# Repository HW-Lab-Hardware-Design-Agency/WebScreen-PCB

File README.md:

# WebScreen-PCB

WebScreen-PCB is the design of a printed circuit board (PCB) for the WebScreen, a display device with a custom stand. This project is developed by **HW Lab - Hardware Design Agency** and aims to optimize the integration and functionality of the WebScreen in various applications.

## Main Features
- **Optimized Design**: Compact and efficient PCB. 
- **Mounting System**: Insertion and friction-based fastening, eliminating the need for adhesives. 
- **Compatibility**: Designed to work with the [DO0200FS01 display](https://www.dwo.net.cn/pd.jsp?id=11919).
- **Connectivity**: Interfaces adapted for easy integration with other devices.
  
## Technical Specifications
- **Size**: 60.6 x 27.6 mm
- **Material**: FR-4 S1000H TG150
- **PCB Thickness**: 1.6 mm
- **Number of Layers**: 4 layers
- **Operating Voltage**: 5V (via usb)
- **Connection Interfaces**: USB / Wi-Fi / Bluetooth

## Included Files
- **Schematic**: : Circuit design in [KiCad](https://www.kicad.org/) format. 
- **PCB Layout**: Board design in Gerber format.
- **Bill of Materials (BOM)**: List of components used. 

## Installation and Usage  
1. Download the Gerber files and send them to a PCB manufacturer.  
2. Acquire the components according to the BOM.  
3. Assemble the PCB.  
4. [Integrate the PCB with the WebScreen](https://www.youtube.com/watch?v=CHH5L84EN5o&t=6s) and perform the corresponding tests.

## License
This project is open source. See the [LICENSE](https://github.com/HW-Lab-Hardware-Design-Agency/WebScreen-PCB/blob/main/LICENSE) file for details.

## PCBWay
[PCBWay](https://pcbway.com/g/j8T652) top quality PCBA service made this project possible: fast, precise, and super reliable. We highly recommend them to all creators out there, and we’ll definitely keep working with them for future builds.

## Contact
For inquiries or contributions, please contact the development team through the repository issues or via email.

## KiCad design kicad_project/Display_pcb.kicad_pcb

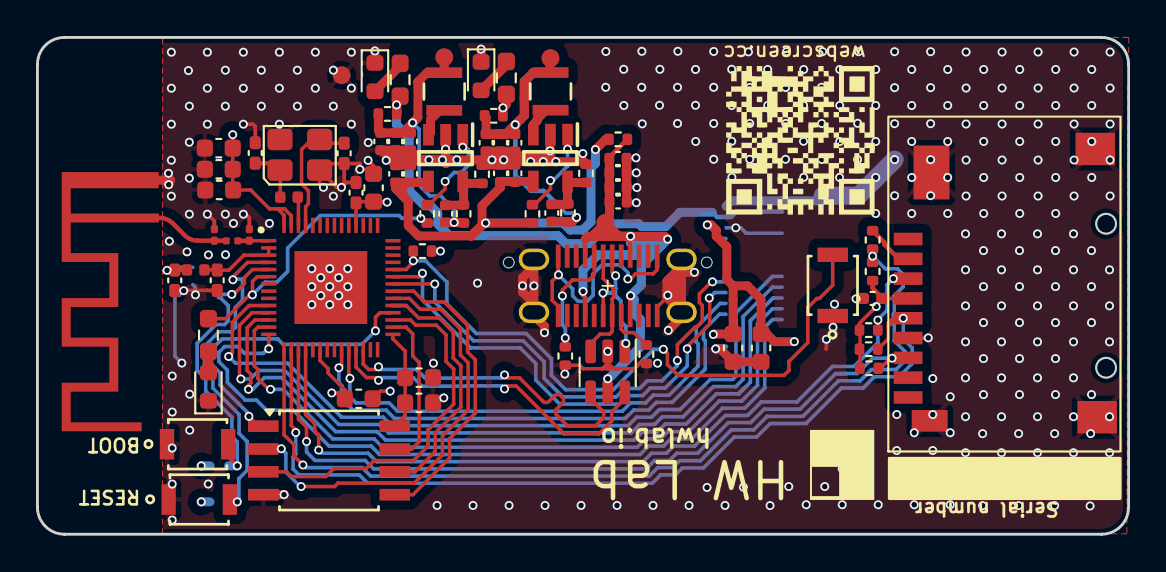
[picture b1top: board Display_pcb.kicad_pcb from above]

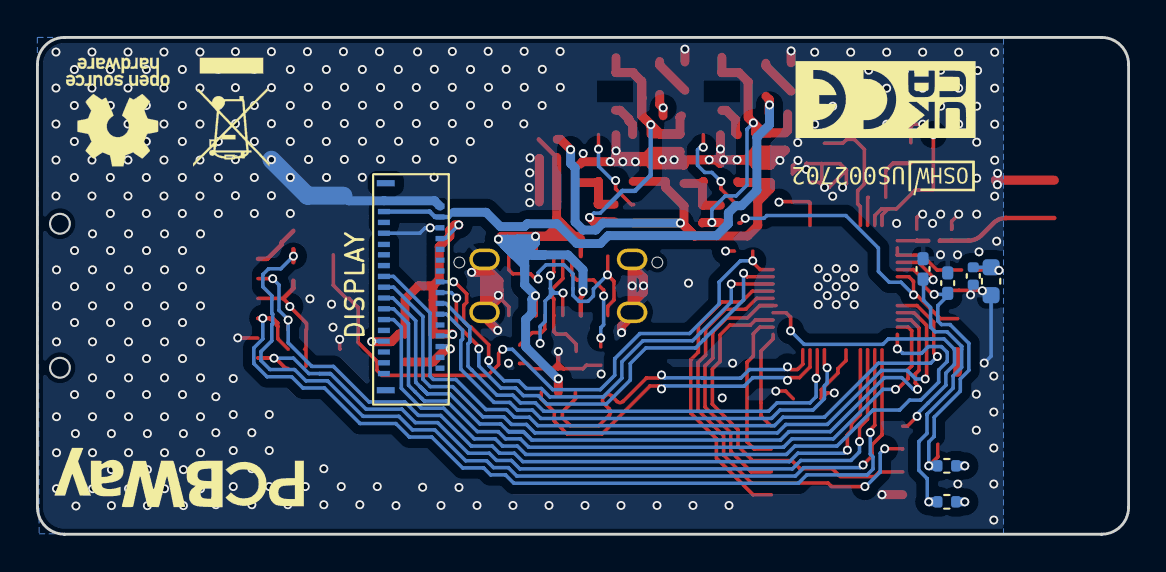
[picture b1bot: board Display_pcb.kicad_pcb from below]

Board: 4 copper layers, 60.6 x 27.6 mm, 86 parts (7 on the bottom side), 56 nets.

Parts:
AE1: PCB Antenna 2.4GHz; pcb_antenna_2_4GHz
C1, C8, C9, C12, C13, C19: 100nF; C_0402_1005Metric_Pad0.74x0.62mm_HandSolder
C2, C5, C6, C7, C10, C14, C15, C20, C32, C33: 1uF; C_0603_1608Metric
C3: 15pF; C_0402_1005Metric_Pad0.74x0.62mm_HandSolder
C4: 12pF; C_0402_1005Metric_Pad0.74x0.62mm_HandSolder
C11: 10uF; C_0402_1005Metric
C16, C17: 1.8pF; C_0201_0603Metric
C18, C22, C24, C25, C27, C28, C30, C34, C36, C37: 22uF; C_0402_1005Metric
C21, C31: 6.8pF; C_0402_1005Metric
C23, C26, C29, C35: 100nF; C_0402_1005Metric
DS1, DS2, DS3: GREEN; LED_0603_1608Metric
IC1: ESP32-S3R8; QFN40P700X700X90-57N-D
J1: Micro_SD_Card_Det_Hirose_DM3AT; TF PUSH
J2: USB C; USB_C_Receptacle_HCTL_HC019-1E1H1A103-0HR
J8: 33FXRH-SM1-GAN-TF
L1: 22nH; L_0402_1005Metric
L2: 2nH; L_0402_1005Metric
L3: 2.7nH; L_0201_0603Metric
L4, L5: 1uH; BR2518_YDN
NT1, NT2: NetTie_2; NetTie-2_SMD_Pad0.5mm
R1, R2, R3, R4, R7, R10, R12, R20: 10k; R_0402_1005Metric
R5, R6: 4k99; R_0402_1005Metric
R8, R18, R19, R32: 0R; R_0402_1005Metric
R9: 64k9; R_0402_1005Metric
R11, R13, R14: 100k; R_0402_1005Metric
R15, R16, R23: 1k; R_0603_1608Metric_Pad0.98x0.95mm_HandSolder
R17: 22k; R_0402_1005Metric
SW1, SW2, SW3: B3U-1000P
TP1: +5V; TestPoint_Pad_D1.0mm
TP2: +4V6; TestPoint_Pad_D1.0mm
TP4: +3V3; TestPoint_Pad_D1.0mm
TP5: GND; TestPoint_Pad_D1.0mm
U1: W25Q128JVSIQ; SOIC-8W_5.3x5.3mm_P1.27mm
U2, U4: SY8089A1AAC; SOT95P285X130-5N
U5: USBLC6-2SC6; SOT-23-6
Y1: 40MHz; SMD32324-4P

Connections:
4.6V: J8.3, J8.4, R16.2, R32.2
+3V3: C1.1, C2.1, C5.1, C6.1, C7.1, C9.1, C10.1, C11.1, C13.1, C15.1, IC1.20 (VDD3P3_RTC), IC1.46 (VDD3P3_CPU), IC1.55 (VDDA_1), IC1.56 (VDDA_2), J1.4 (VDD), J8.8, L2.1, NT1.2, NT2.2, R1.1, R2.1, R3.1, R4.1, R7.1, R12.1, R18.2, R20.1, R23.2
/AVDD: C32.1, J8.27, NT1.1
/CLK: IC1.16 (GPIO11), J1.5 (CLK), R4.2
/CMD: IC1.18 (GPIO13), J1.3 (CMD), R12.2
/CS: IC1.15 (GPIO10), R8.2, R20.2
/D+: J2.A6 (D+), J2.B6 (D+), U5.3 (I/O2)
/D-: J2.A7 (D-), J2.B7 (D-), U5.1 (I/O1)
/DAT0: IC1.17 (GPIO12), J1.7 (DAT0), R3.2
/Flash_Memory/SPICLK: IC1.33 (SPICLK), U1.6 (CLK)
/Flash_Memory/SPICS0: IC1.32 (SPICS0), U1.1 (~CS)
/Flash_Memory/SPID: IC1.35 (SPID), U1.5 (DI(IO0))
/Flash_Memory/SPIHD: IC1.30 (SPIHD), U1.7 (IO3)
/Flash_Memory/SPIQ: IC1.34 (SPIQ), U1.2 (DO(IO1))
/Flash_Memory/SPIWP: IC1.31 (SPIWP), U1.3 (IO2)
/MCU/GPIO0: C19.1, IC1.5 (GPIO0), R2.2, SW2.2
/MCU/GPIO1: IC1.6 (GPIO1), R11.2, R15.2
/MCU/GPIO33: IC1.38 (GPIO33), R7.2, SW3.2
/MCU/LNA: C16.1, IC1.1 (LNA_IN), L3.2
/MCU/LNA_IN: AE1.1 (FP), C17.1, L3.1
/OL_CS: IC1.11 (GPIO6), J8.17
/OL_D0: IC1.24 (GPIO18), J8.20
/OL_D1: IC1.12 (GPIO7), J8.19
/OL_D2: IC1.36 (SPICLK_N), J8.16
/OL_D3: IC1.10 (GPIO5), J8.15
/OL_RESET: IC1.23 (GPIO17), J8.22
/OL_SCK: IC1.37 (SPICLK_P), J8.18
/OL_SD0: IC1.13 (GPIO8), J8.21
/OL_TE: IC1.14 (GPIO9), J8.23
/POWER/VBUS: C18.1, C27.1, C28.1, C37.1, J2.A4 (VBUS), J2.A9 (VBUS), J2.B4 (VBUS), J2.B9 (VBUS), R19.1, TP1.1, U5.5 (VBUS)
/USB+: IC1.26 (GPIO20), U5.4 (I/O2)
/USB-: IC1.25 (GPIO19), U5.6 (I/O1)
GND: AE1.2 (GND), C1.2, C2.2, C3.2, C4.2, C5.2, C6.2, C7.2, C8.2, C9.2, C10.2, C11.2, C12.2, C13.2, C14.2, C15.2, C16.2, C17.2, C18.2, C19.2, C20.2, C22.2, C23.2, C24.2, C25.2, C26.2, C27.2, C28.2, C29.2, C30.2, C32.2, C33.2, C34.2, C35.2, C36.2, C37.2, DS1.1 (K), DS2.1 (K), DS3.1 (K), IC1.57 (EP), J1.6 (VSS), J1.11 (SHIELD), J2.A1 (GND), J2.S1 (SHIELD), J8.1, J8.2, J8.6, J8.7, J8.28, R5.2, R6.2, R10.2, R17.2, SW1.1, SW2.1, SW3.1, TP5.1, U1.4 (GND), U2.2 (GND), U4.2 (GND), U5.2 (GND), Y1.2, Y1.4
unnamed: C4.1, L1.1, Y1.1
unnamed: C21.1, C22.1, C23.1, C24.1, L5.2, R9.1, R32.1, TP2.1
unnamed: C31.1, C34.1, C35.1, C36.1, L4.2, R14.1, R18.1, TP4.1
unnamed: DS1.2 (A), R15.1
unnamed: DS2.2 (A), R16.1
unnamed: DS3.2 (A), R23.1
unnamed: C12.1, IC1.4 (CHIP_PU), R1.2, SW1.2
unnamed: C8.1, IC1.2 (VDD3P3_1), IC1.3 (VDD3P3_2), L2.2
unnamed: C3.1, IC1.53 (XTAL_N), Y1.3
unnamed: IC1.54 (XTAL_P), L1.2
unnamed: J1.2 (DAT3/CD), R8.1
unnamed: J2.A5 (CC1), R6.1
unnamed: J2.B5 (CC2), R5.1
unnamed: J2.A12 (GND), J2.B1 (GND), J2.B12 (GND)
unnamed: C33.1, J8.26, NT2.1
unnamed: R11.1, U2.1 (EN)
unnamed: C21.2, R9.2, R10.1, U2.5 (FB)
unnamed: L5.1, U2.3 (LX)
unnamed: R13.1, U4.1 (EN)
unnamed: C31.2, R14.2, R17.1, U4.5 (FB)
unnamed: L4.1, U4.3 (LX)
VCC: C25.1, C26.1, C29.1, C30.1, R13.2, R19.2, U2.4 (IN), U4.4 (IN)
VDD_SPI: C14.1, C20.1, IC1.29 (VDD_SPI), U1.8 (VCC)

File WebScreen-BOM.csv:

Reference,Value,Qty,DNP,BOM,LCSC Part #,MPN
AE1,PCB Antenna 2.4GHz,1,,,,
"C1,C8,C9,C12,C13,C19,C23,C26,C29,C35",100nF,10,,35V 100nF X7R ±10% 0402 Multilayer Ceramic Capacitors MLCC - SMD/SMT ROHS,C343047,CGA2B3X7R1V104KT0Y0F
"C2,C5,C6,C7,C10,C14,C15,C20,C32,C33",1uF,10,,16V 1uF X5R ±10% 0603 Multilayer Ceramic Capacitors MLCC - SMD/SMT ROHS,C1592,CL10A105KO8NNNC
C3,15pF,1,,16V 15pF NP0 ±10% 0402 Multilayer Ceramic Capacitors MLCC - SMD/SMT ROHS,C1852854,CC0402KRNPO7BN150
C4,12pF,1,,25V 12pF null ±2% 0402 Multilayer Ceramic Capacitors MLCC - SMD/SMT ROHS,C882545,GRM1555C1E120GA01D
"C11,C18",10uF,2,,10V 10uF X5R ±20% 0402 Multilayer Ceramic Capacitors MLCC - SMD/SMT ROHS,C315248,CL05A106MP5NUNC
"C16,C17",1.8pF,2,,50V 1.8pF C0G 0201 Multilayer Ceramic Capacitors MLCC - SMD/SMT ROHS, C161415, GRM0335C1H1R8BA01D
"C21,C31",6.8pF,2,,50V 6.8pF C0G 0402 Multilayer Ceramic Capacitors MLCC - SMD/SMT ROHS,C1576,0402CG6R8C500NT
"C22,C24,C25,C30,C34,C36",22uF,6,,10V 22uF X5R ±20% 0402 Multilayer Ceramic Capacitors MLCC - SMD/SMT ROHS,C6119813,CGA0402X5R226M100GT
"DS1,DS2,DS3",GREEN,3,,LED GREEN [0603],C125098,LTST-C191KGKT
IC1,ESP32-S3R8,1,,"WiFi Modules - 802.11 SMD IC, Dual-Core MCU, Wi-Fi 2.4G & BLE 5.0 Combo, 8 MB Octal SPI PSRAM, QFN 56-pin, 7*7 mm",C2913194,ESP32-S3R8
J1,Micro_SD_Card_Det_Hirose_DM3AT,1,,-20℃~+90℃ 2mm Deck MicroSD card (TF card) Self bomb SMD SD Card / Memory Card Connector ROHS,C393941,TF PUSH
J2,USB C,1,,,C2894918,HC019-1E1H1A103-0HR
J8,33FXRH-SM1-GAN-TF,1,,"SMD,P=0.6mm FFC/FPC Connectors ROHS",C2890488,33FXRH-SM1-GAN-TF
L1,22nH,1,,300mA 22nH ±5% 600mΩ 0402 Inductors (SMD) ROHS,C15178,SDCL1005C22NJTDF
L2,2nH,1,,300mA 2nH 200mΩ 0402 Inductors (SMD) ROHS,C279790,SDCL1005C2N0BTDF
L3,2.7nH,1,,500mA 2.7nH 200mΩ 0201 Inductors (SMD) ROHS,C98043, LQP03TN2N7B02D
"L4,L5",1uH,2,,1.2A 1uH ±20% 1.2A 1007 Power Inductors ROHS,C524998,BRFL2518T1R0M
"Q1,Q3",S8050,2,, 25V 300mW 500mA NPN SOT-23 Bipolar (BJT) ROHS ,C181158, S8050
Q2,BSS84,1,," 50V 130mA 200mW 10Ω@5V,100mA 2.5V@250uA 1 Piece P-Channel SOT-23 MOSFETs ROHS",C2926187, IRF4905STRLP(UMW)
"R1,R2,R3,R4,R12",10k,5,,62.5mW Thick Film Resistors 50V ±100ppm/℃ ±5% 10kΩ 0402 Chip Resistor - Surface Mount ROHS,C25531,0402WGJ0103TCE
"R5,R6",4k99,2,,62.5mW Thick Film Resistors 50V ±100ppm/℃ ±1% 4.99kΩ 0402 Chip Resistor - Surface Mount ROHS,C137965,RC0402FR-074K99L
"R7,R11,R13,R14,R30",100k,5,,62.5mW Thick Film Resistors 50V ±100ppm/℃ ±1% 100kΩ 0402 Chip Resistor - Surface Mount ROHS,C25741,0402WGF1003TCE
"R9,R10",TBD,2,,,,
"R15,R16,R23",1k,3,,RES SMD 1k 1% [0603],C844746,CRCW06031K00FKEAC
R17,22k,1,,62.5mW Thick Film Resistors 50V ±100ppm/℃ ±1% 22kΩ 0402 Chip Resistor - Surface Mount ROHS,C25768,0402WGF2202TCE
"R18,R19,R21,R32",0R,4,,62.5mW Thick Film Resistors 50V ±800ppm/℃ ±1% 0Ω 0402 Chip Resistor - Surface Mount ROHS,C17168,0402WGF0000TCE
R31,680k,1,,62.5mW Thick Film Resistors 50V ±100ppm/℃ ±1% 680kΩ 0402 Chip Resistor - Surface Mount ROHS,C163456,RC0402FR-07680KL
"SW1,SW2,SW3",B3U-1000P,3,,"2.5mm 1.6mm Round Button 50mA Brick nogging 3mm SPST 153gf 12V SMD,2.5x3mm Tactile Switches ROHS",C231329,B3U-1000P
U1,W25Q128JVSIQ,1,,128Mbit SOIC-8-208mil NOR FLASH ROHS,C113767,W25Q128JVSIQ
"U2,U4",SY8089A1AAC,2,,LOW LOSS POWER DISTRIBUTION SWITCH WITH,C479074,SY8089A1AAC
U5,USBLC6-2SC6,1,,5A 17V 6V Unidirectional 5.25V SOT-23-6 Electrostatic and Surge Protection (TVS/ESD) ROHS,C7519,USBLC6-2SC6
Y1,40MHz,1,,40MHz 贴片晶振 15pF ±10ppm ±20ppm SMD3225-4P Crystals ROHS,C9010,X322540MPB4SI

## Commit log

2024-11-02 Added layout and schematics files.
2024-11-02 Added BOM csv file.
2024-11-25 Added Kikad profile files.
2025-02-19 Pcb to production
2025-02-19 Change LICENSE
2025-03-26 Remove USB preregulator from power circuit
2025-06-30 Expose copper on Bluetooth/Wifi antenna (removed front mask)
2025-07-08 Design revision: SD improvements, flash update, silkscreen and USB differential fix
2025-07-18 Change SD card power source from VDD_SPI to 3V3 to support A1 cards
2025-08-26 Add file Technical Note for PCB Manufacturing
2025-08-28 Change logos PcbWay and UK-CA-CE certification

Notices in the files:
README.md:
License: CERN-OHL-P-2.0
